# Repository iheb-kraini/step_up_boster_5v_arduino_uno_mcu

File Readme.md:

Digitally Regulated Boost Converter (Arduino Uno PID)

A closed-loop DC-DC Step-Up (Boost) Converter driven by an Arduino Uno R3. The system continuously samples output voltage through a $10\text{ k}\Omega + 10\text{ k}\Omega$ feedback divider, processes the reading through an Exponential Moving Average (EMA) filter, executes a $1\text{ kHz}$ discrete PID loop with anti-windup, and updates a custom $10\text{ kHz}$ Fast PWM signal on Timer 1.
---

## Features

* **Firmware:** Written for Arduino Uno R3 (ATmega328P).
* **Simulation:** Full circuit simulation in Proteus.
* **Hardware:** Custom PCB designed in KiCad.
* **Power Supply:** Input range `3V–4.2V DC` via terminal block.

---

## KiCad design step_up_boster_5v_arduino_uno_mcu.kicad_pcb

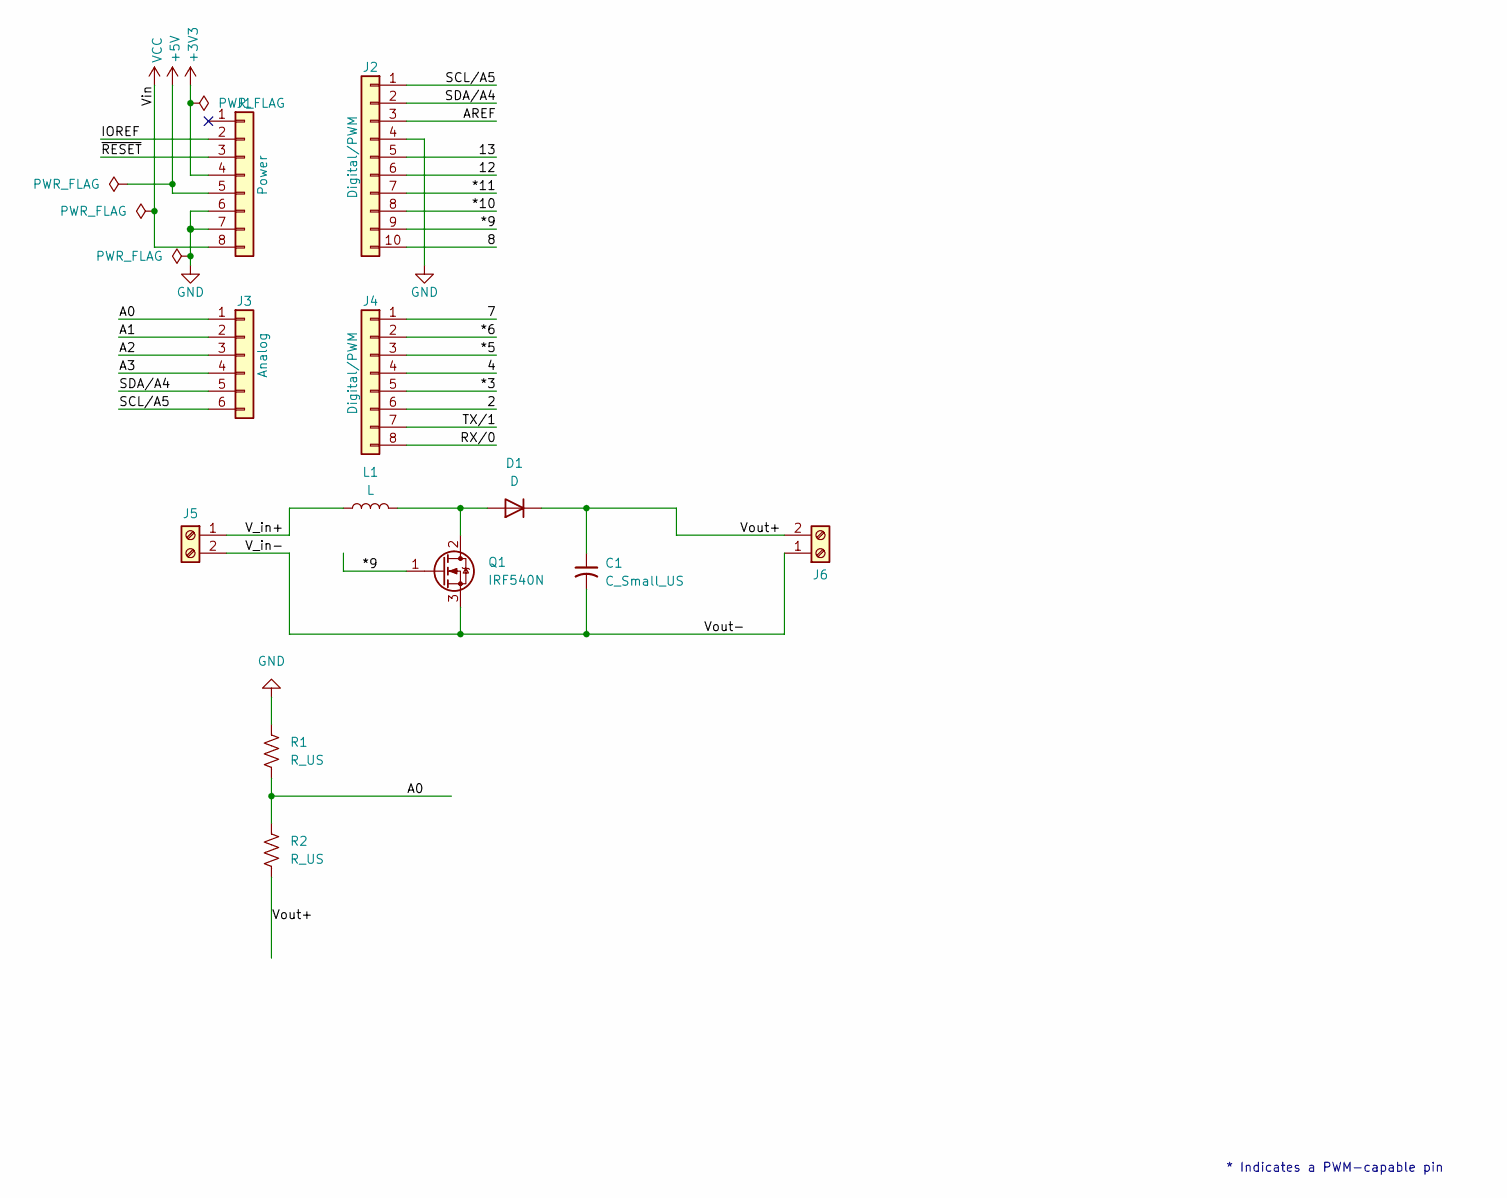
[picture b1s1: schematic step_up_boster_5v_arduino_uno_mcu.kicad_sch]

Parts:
C1: C_Small_US; CP_Radial_D10.0mm_P2.50mm
D1: D; D_DO-41_SOD81_P10.16mm_Horizontal
J1: Power; PinSocket_1x08_P2.54mm_Vertical
J2: Digital/PWM; PinSocket_1x10_P2.54mm_Vertical
J3: Analog; PinSocket_1x06_P2.54mm_Vertical
J4: Digital/PWM; PinSocket_1x08_P2.54mm_Vertical
J5, J6: Screw_Terminal_01x02; TerminalBlock_Phoenix_MKDS-1,5-2-5.08_1x02_P5.08mm_Horizont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
L1: L; L_Axial_L16.0mm_D9.5mm_P20.32mm_Horizontal_Vishay_IM-10-37
Q1: IRF540N; TO-220-3_Vertical
R1, R2: R_US; R_Axial_DIN0309_L9.0mm_D3.2mm_P12.70mm_Horizontal

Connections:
+3V3: J1.4
+5V: J1.5
/2: J4.6
/4: J4.4
/7: J4.1
/8: J2.10
/12: J2.6
/13: J2.5
/*3: J4.5
/*5: J4.3
/*6: J4.2
/*9: J2.9, Q1.1 (G)
/*10: J2.8
/*11: J2.7
/A0: J3.1, R1.2, R2.1
/A1: J3.2
/A2: J3.3
/A3: J3.4
/AREF: J2.3
/IOREF: J1.2
/RX/0: J4.8
/SCL/A5: J2.1, J3.6
/SDA/A4: J2.2, J3.5
/TX/1: J4.7
/V_in+: J5.1, L1.1
/V_in-: C1.2, J5.2, J6.1, Q1.3 (S)
/Vout+: C1.1, D1.1 (K), J6.2, R2.2
/~RESET: J1.3
GND: J1.6, J1.7, J2.4, R1.1
unnamed: D1.2 (A), L1.2, Q1.2 (D)
VCC: J1.8

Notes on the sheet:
* Indicates a PWM-capable pin

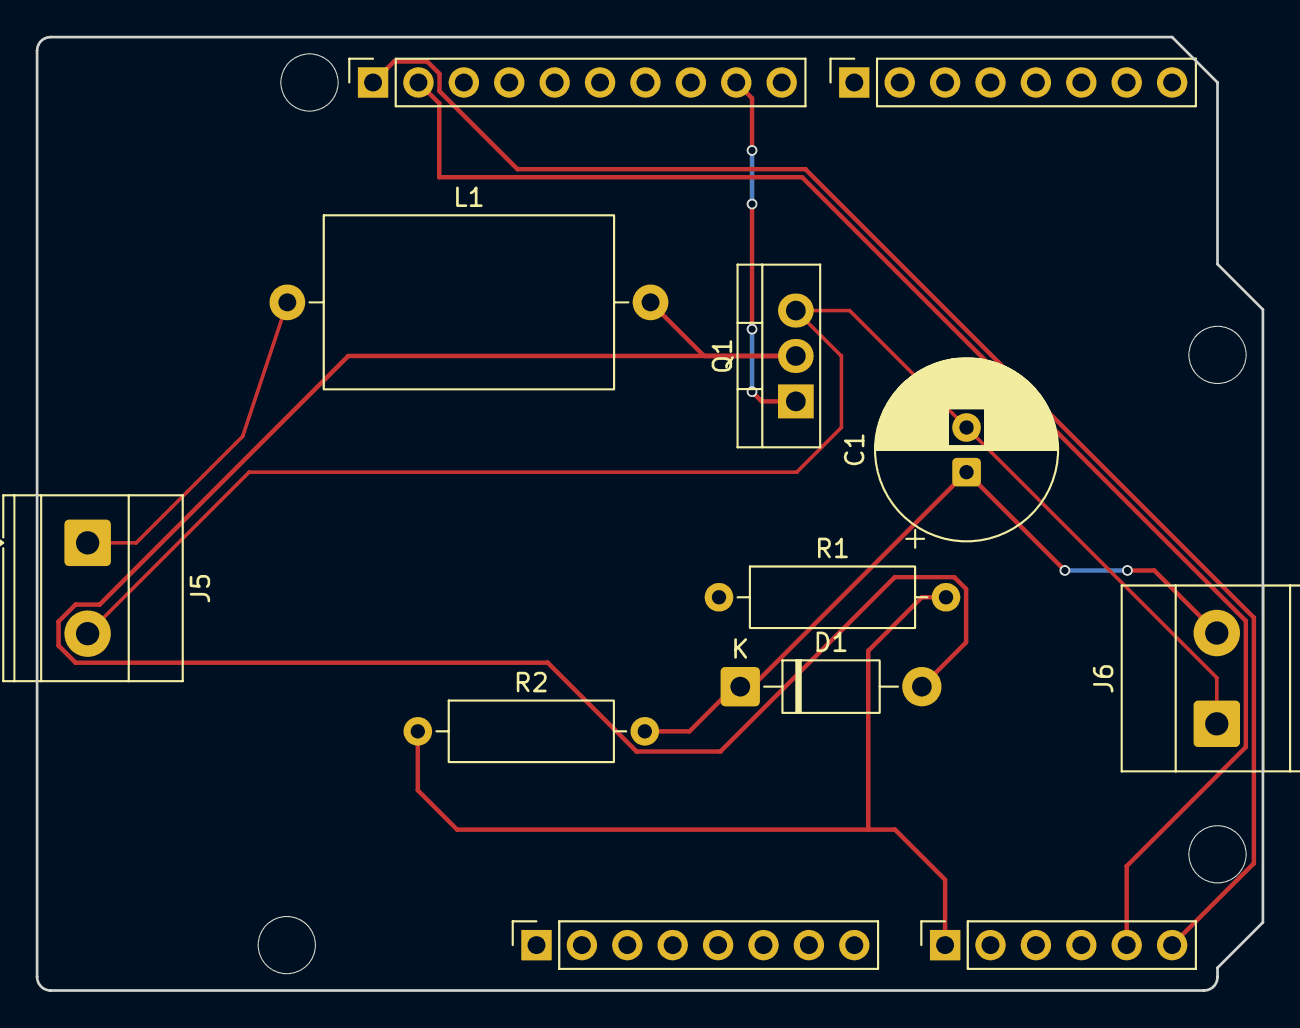
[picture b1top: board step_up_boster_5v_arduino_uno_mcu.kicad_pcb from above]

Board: 2 copper layers, 68.6 x 53.3 mm, 16 parts (0 on the bottom side), 9 nets.

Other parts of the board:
MH1, MH2, MH3, MH4: MountingHole_3.2mm
